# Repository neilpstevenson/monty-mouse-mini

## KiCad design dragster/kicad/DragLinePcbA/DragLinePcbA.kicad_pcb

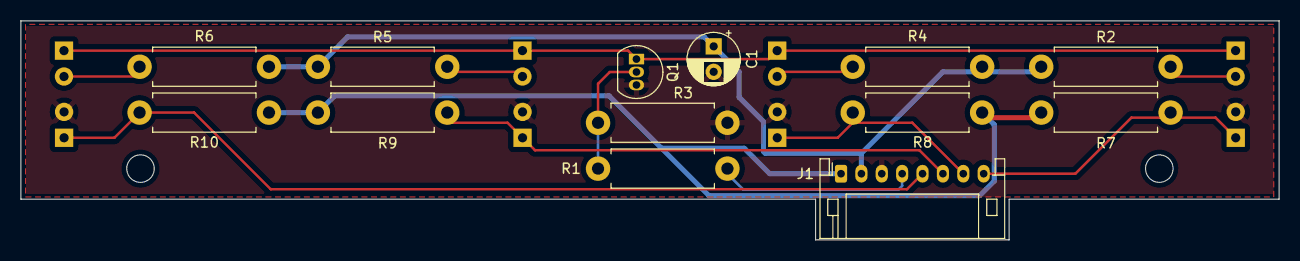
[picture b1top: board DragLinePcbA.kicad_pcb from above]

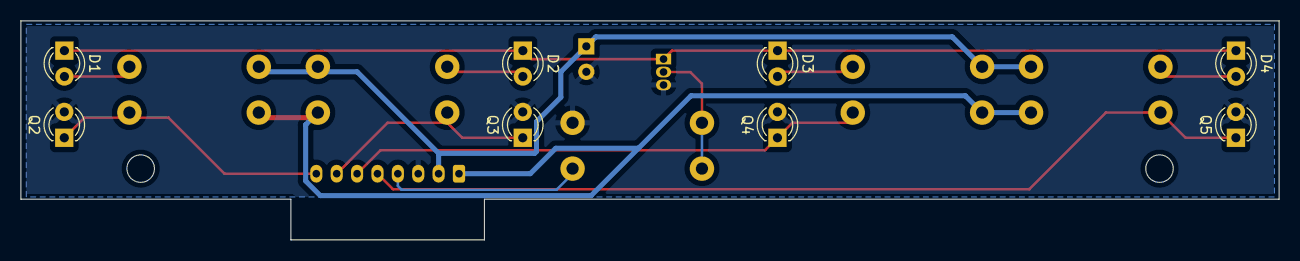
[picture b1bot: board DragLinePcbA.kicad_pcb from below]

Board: 2 copper layers, 123.5 x 21.5 mm, 21 parts (8 on the bottom side), 14 nets.

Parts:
C1: 100uF; CP_Radial_D5.0mm_P2.50mm
D1, D2, D3, D4: LED; LED_D3.0mm_Clear
J1: Conn_01x08_Male; JST_PH_S8B-PH-K_1x08_P2.00mm_Horizontal
Q1: BC337; TO-92_Inline
Q2, Q3, Q4, Q5: SFH309; LED_D3.0mm_Clear
R1: 270R; R_Axial_DIN0411_L9.9mm_D3.6mm_P12.70mm_Horizontal
R2, R4, R5, R6: 27R; R_Axial_DIN0411_L9.9mm_D3.6mm_P12.70mm_Horizontal
R3: 10k; R_Axial_DIN0411_L9.9mm_D3.6mm_P12.70mm_Horizontal
R7, R8, R9, R10: 1.5k; R_Axial_DIN0411_L9.9mm_D3.6mm_P12.70mm_Horizontal

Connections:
+3V3: J1.1, R7.1, R8.1, R9.1, R10.1
+BATT: C1.1, J1.2, R2.1, R4.1, R5.1, R6.1
A0: J1.5, Q5.1 (C), R10.2
A1: J1.6, Q4.1 (C), R9.2
A2: J1.7, Q3.1 (C), R8.2
A3: J1.8, Q2.1 (C), R7.2
D12: J1.4, R1.1
GND: C1.2, J1.3, Q1.3 (E), Q2.2 (E), Q3.2 (E), Q4.2 (E), Q5.2 (E), R3.2
unnamed: D1.1 (K), D2.1 (K), D3.1 (K), D4.1 (K), Q1.1 (C)
unnamed: D1.2 (A), R2.2
unnamed: D2.2 (A), R4.2
unnamed: D3.2 (A), R5.2
unnamed: D4.2 (A), R6.2
unnamed: Q1.2 (B), R1.2, R3.1

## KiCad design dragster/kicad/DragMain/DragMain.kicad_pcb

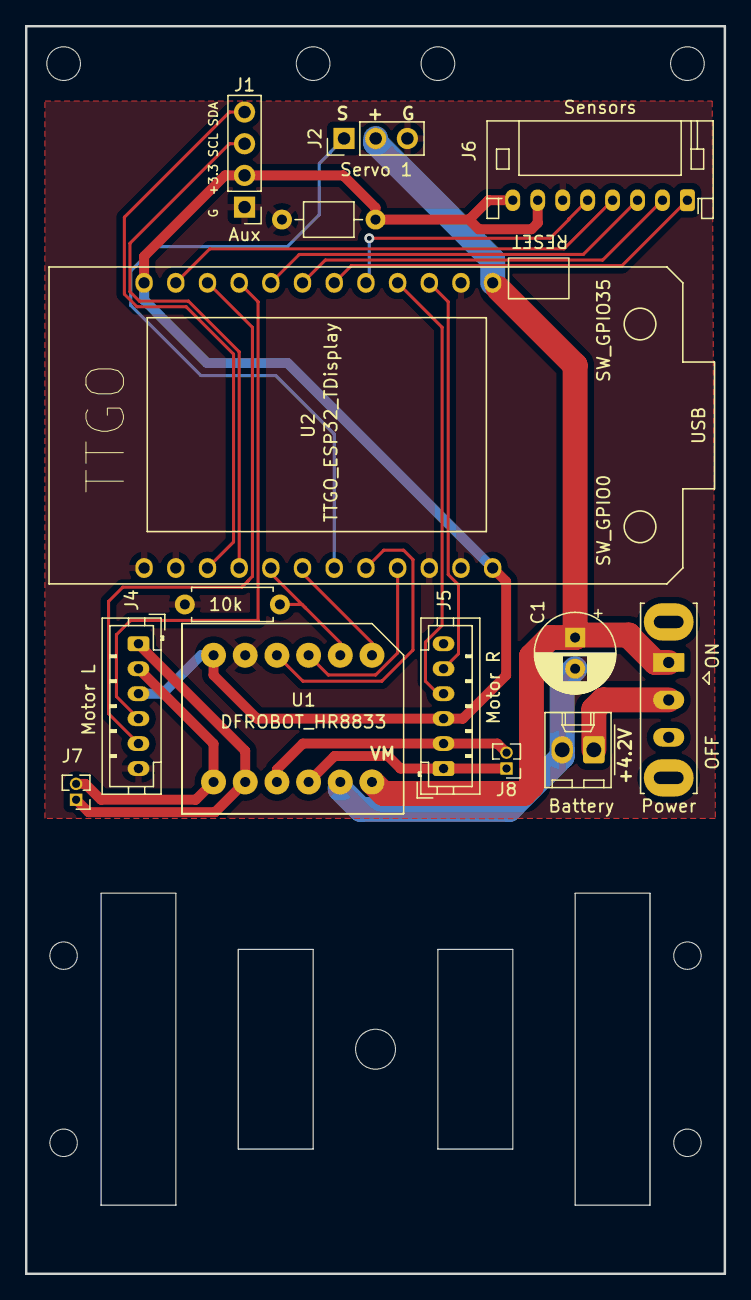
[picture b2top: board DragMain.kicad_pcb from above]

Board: 2 copper layers, 56.0 x 100.0 mm, 14 parts (0 on the bottom side), 24 nets.

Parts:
C1: 330uF; CP_Radial_D6.3mm_P2.50mm
C2: 0.1uF; C_Axial_L3.8mm_D2.6mm_P7.50mm_Horizontal
J1: Aux; PinHeader_1x04_P2.54mm_Vertical
J2: Servo 1; PinHeader_1x03_P2.54mm_Vertical
J3: Battery; Molex_KK-254_AE-6410-02A_1x02_P2.54mm_Vertical
J4: Motor L; JST_PH_B6B-PH-K_1x06_P2.00mm_Vertical
J5: Motor R; JST_PH_B6B-PH-K_1x06_P2.00mm_Vertical
J6: Sensors; JST_PH_S8B-PH-K_1x08_P2.00mm_Horizontal
J7: Motor L2; PinHeader_1x02_P1.27mm_Vertical
J8: Motor R2; PinHeader_1x02_P1.27mm_Vertical
Power: SW_SPST; SW_Slide_1P2T_CK_OS102011MS2Q
R1: 10k; R_Axial_DIN0207_L6.3mm_D2.5mm_P7.62mm_Horizontal
U1: DFROBOT_HR8833
U2: TTGO_ESP32_TDisplay; TTGO_ESP32_TDisplay_New

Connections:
+3V3: C2.2, J1.2, J4.3, J5.3, J6.7, J6.8, U1.6 (VCC), U2.12 (3V3), U2.24 (3V3)
+BATT: C1.1, J2.2, Power.1 (A), U1.12 (VM), U2.13 (5V)
GND: C1.2, C2.1, J1.1, J2.3, J3.2, J4.6, J5.6, J6.6, R1.2, U1.5 (GND), U1.11 (GND), U2.1 (GND), U2.2 (GND), U2.10 (GND), U2.11 (GND), U2.14 (GND)
GPIO2: U1.1 (IA1), U2.6 (IO2)
GPIO12: U1.3 (IB1), U2.9 (IO12)
GPIO13: U1.4 (IB2), U2.8 (IO13)
GPIO15: J2.1, U2.7 (IO15)
GPIO17: R1.1, U1.2 (IA2), U2.5 (IO17)
GPIO21: J1.4, U2.3 (IO21)
GPIO22: J1.3, U2.4 (IO22)
GPIO25: J6.5, U2.17 (IO25)
GPIO26: J5.4, U2.16 (IO26)
GPIO27: J5.5, U2.15 (IO27)
GPIO32: J6.2, U2.19 (IO32)
GPIO33: J6.1, U2.18 (IO33)
GPIO36: J6.4, U2.23 (IO36)
GPIO37: J4.5, U2.22 (IO37)
GPIO38: J4.4, U2.21 (IO38)
GPIO39: J6.3, U2.20 (IO39)
unnamed: J3.1, Power.2 (B)
unnamed: J4.2, J7.2, U1.7 (MA2)
unnamed: J4.1, J7.1, U1.8 (MA1)
unnamed: J5.2, J8.2, U1.9 (MB2)
unnamed: J5.1, J8.1, U1.10 (MB1)

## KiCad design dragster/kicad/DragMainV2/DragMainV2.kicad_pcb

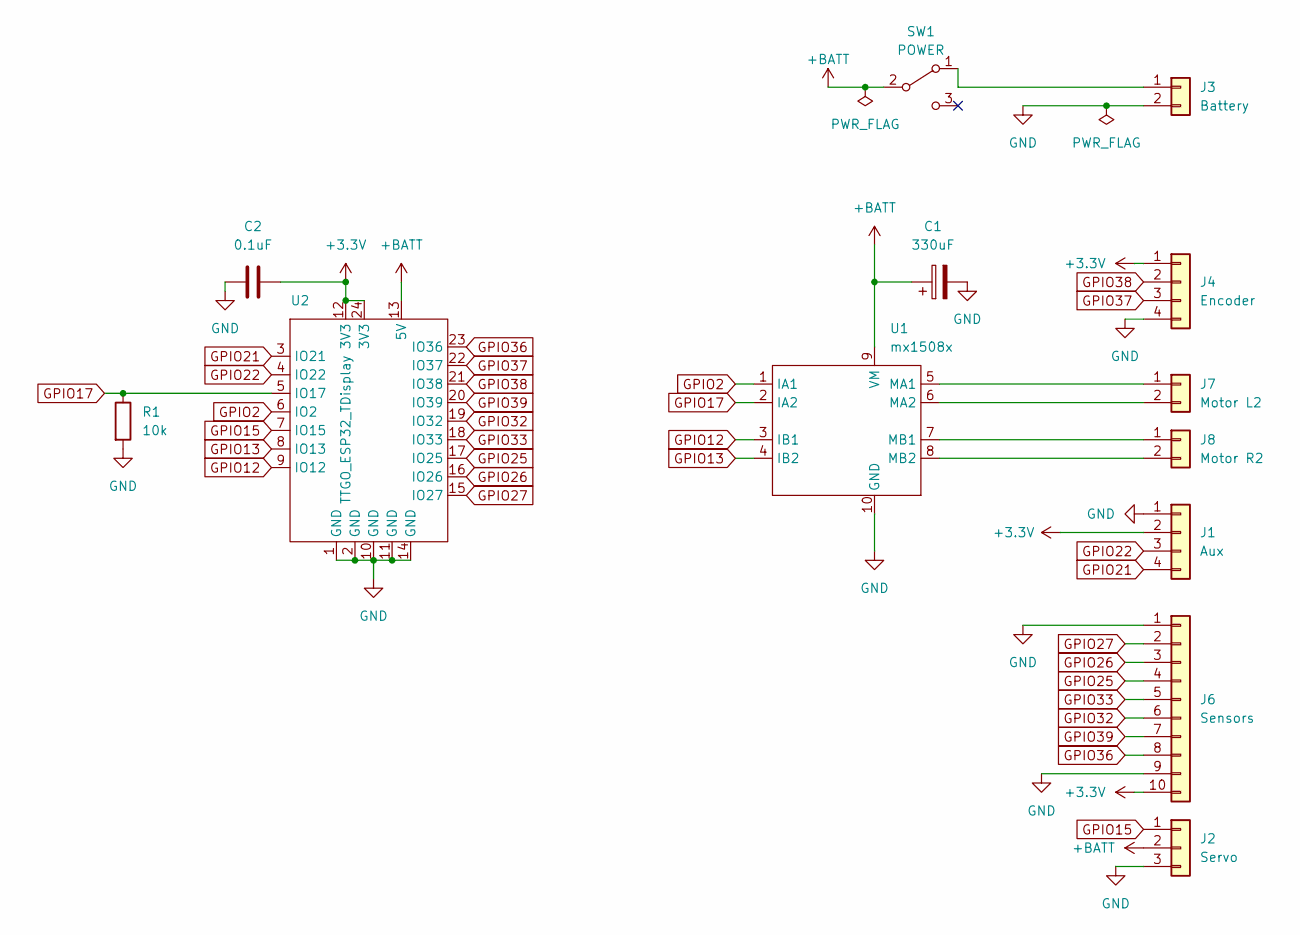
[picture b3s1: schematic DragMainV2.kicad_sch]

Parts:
C1: 330uF; CP_Radial_D6.3mm_P2.50mm
C2: 0.1uF; C_Axial_L3.8mm_D2.6mm_P7.50mm_Horizontal
J1: Aux; PinHeader_1x04_P2.54mm_Vertical
J2: Servo; PinHeader_1x03_P2.54mm_Vertical
J3: Battery; Molex_KK-254_AE-6410-02A_1x02_P2.54mm_Vertical
J4: Encoder; JST_PH_S4B-PH-K_1x04_P2.00mm_Horizontal
J6: Sensors; JST_PH_S10B-PH-K_1x10_P2.00mm_Horizontal
J7: Motor L2; PinHeader_1x02_P1.27mm_Vertical
J8: Motor R2; PinHeader_1x02_P1.27mm_Vertical
R1: 10k; R_Axial_DIN0207_L6.3mm_D2.5mm_P7.62mm_Horizontal
SW1: POWER; SW_Slide_1P1T_Power-Neil
U1: mx1508x
U2: TTGO_ESP32_TDisplay; TTGO_ESP32_TDisplay_New

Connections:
+3.3V: C2.2, J1.2, J4.1, J6.10, U2.12 (3V3), U2.24 (3V3)
+BATT: C1.1, J2.2, SW1.2 (B), U1.9 (VM), U2.13 (5V)
GND: C1.2, C2.1, J1.1, J2.3, J3.2, J4.4, J6.1, J6.9, R1.2, U1.10 (GND), U2.1 (GND), U2.2 (GND), U2.10 (GND), U2.11 (GND), U2.14 (GND)
GPIO2: U1.1 (IA1), U2.6 (IO2)
GPIO12: U1.3 (IB1), U2.9 (IO12)
GPIO13: U1.4 (IB2), U2.8 (IO13)
GPIO15: J2.1, U2.7 (IO15)
GPIO17: R1.1, U1.2 (IA2), U2.5 (IO17)
GPIO21: J1.4, U2.3 (IO21)
GPIO22: J1.3, U2.4 (IO22)
GPIO25: J6.4, U2.17 (IO25)
GPIO26: J6.3, U2.16 (IO26)
GPIO27: J6.2, U2.15 (IO27)
GPIO32: J6.6, U2.19 (IO32)
GPIO33: J6.5, U2.18 (IO33)
GPIO36: J6.8, U2.23 (IO36)
GPIO37: J4.3, U2.22 (IO37)
GPIO38: J4.2, U2.21 (IO38)
GPIO39: J6.7, U2.20 (IO39)
unnamed: J7.1, U1.5 (MA1)
unnamed: J7.2, U1.6 (MA2)
unnamed: J8.1, U1.7 (MB1)
unnamed: J8.2, U1.8 (MB2)
unnamed: J3.1, SW1.1 (A)

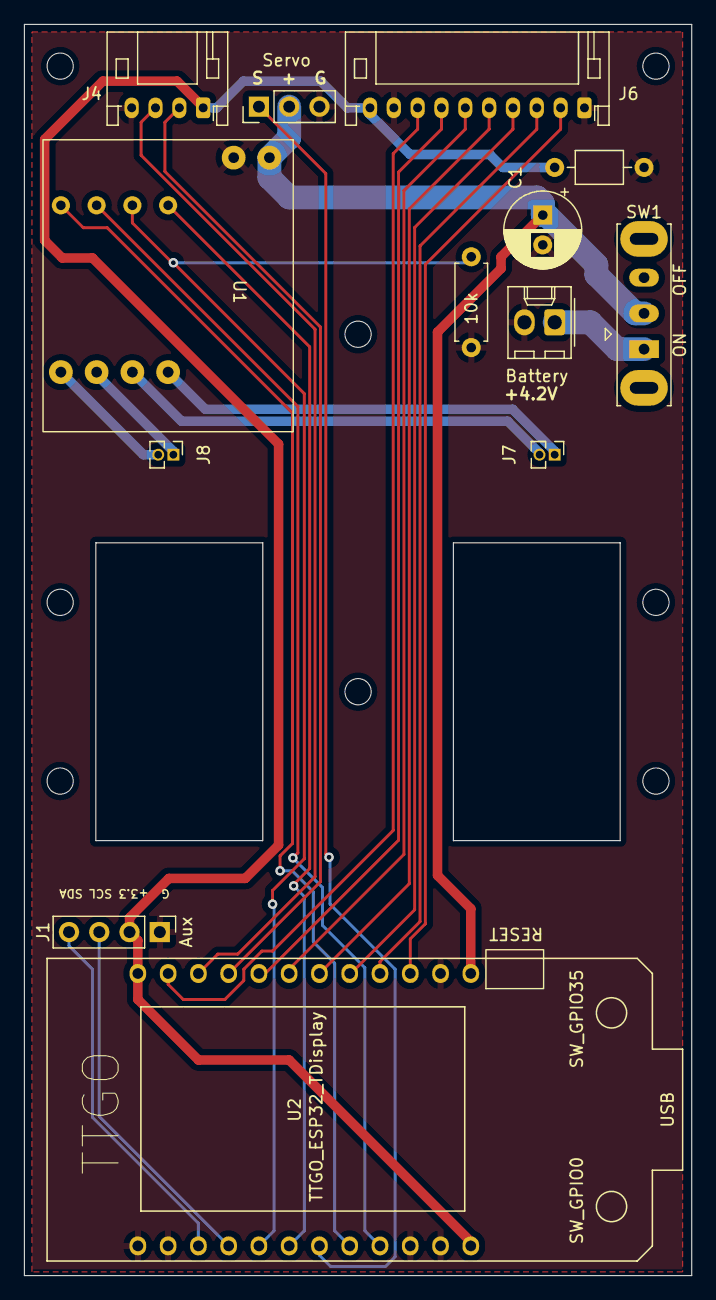
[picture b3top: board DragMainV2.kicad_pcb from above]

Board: 2 copper layers, 56.0 x 105.0 mm, 21 parts (0 on the bottom side), 24 nets.

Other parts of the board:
REFholecentre: locked; MountingHole_2.2mm_M2
REFholeftmr: locked; MountingHole_2.2mm_M2
REFholeleft: locked; MountingHole_2.2mm_M2
REFholemidfront: locked; MountingHole_2.2mm_M2
REFholeright: locked; MountingHole_2.2mm_M2
REFholerightmf: locked; MountingHole_2.2mm_M2
REFholerightmr: locked; MountingHole_2.2mm_M2
REFleftmf: locked; MountingHole_2.2mm_M2

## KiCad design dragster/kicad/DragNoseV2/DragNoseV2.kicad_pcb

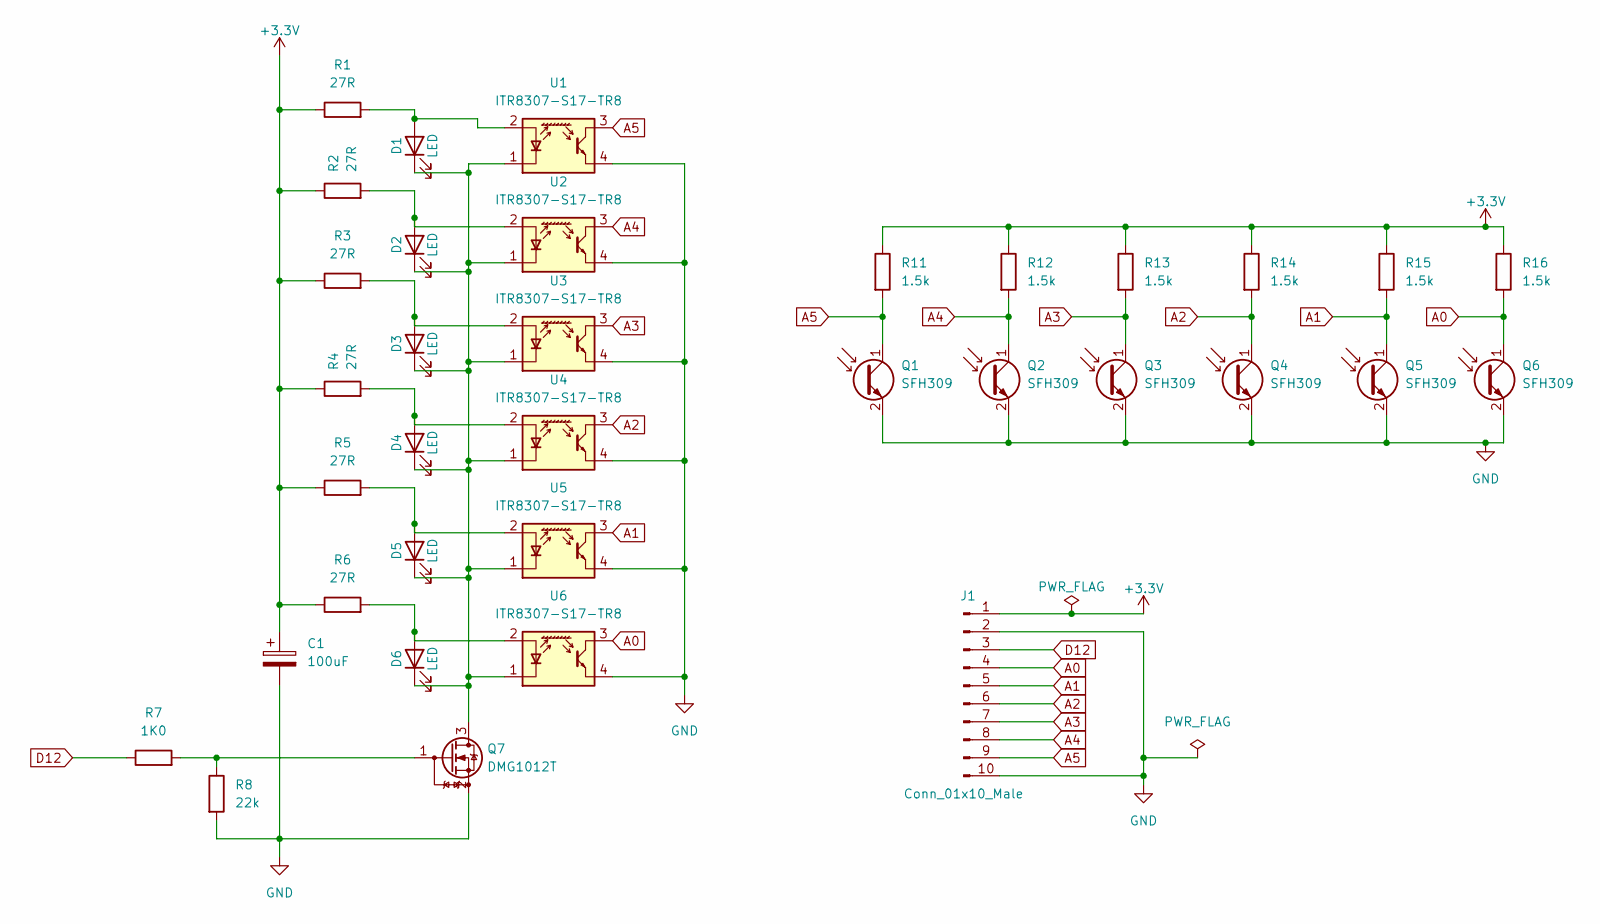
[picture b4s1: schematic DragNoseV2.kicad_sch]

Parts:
C1: 100uF; C_Elec_5x5.8
D1, D2, D3, D4, D5, D6: LED; LED_D3.0mm_Clear
J1: Conn_01x10_Male; JST_PH_S10B-PH-K_1x10_P2.00mm_Horizontal
Q1, Q2, Q3, Q4, Q5, Q6: SFH309; LED_D3.0mm_Clear
Q7: DMG1012T; SOT-523
R1, R2, R3, R4, R5, R6: 27R; R_0805_2012Metric_Pad1.20x1.40mm_HandSolder
R7: 1K0; R_0805_2012Metric_Pad1.20x1.40mm_HandSolder
R8: 22k; R_0805_2012Metric_Pad1.20x1.40mm_HandSolder
R11, R12, R13, R14, R15, R16: 1.5k; R_0805_2012Metric_Pad1.20x1.40mm_HandSolder
U1, U2, U3, U4, U5, U6: ITR8307-S17-TR8; Everlight_ITR1201SR10AR

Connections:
+3.3V: C1.1, J1.1, R1.1, R2.1, R3.1, R4.1, R5.1, R6.1, R11.1, R12.1, R13.1, R14.1, R15.1, R16.1
A0: J1.4, Q6.1 (C), R16.2, U6.3
A1: J1.5, Q5.1 (C), R15.2, U5.3
A2: J1.6, Q4.1 (C), R14.2, U4.3
A3: J1.7, Q3.1 (C), R13.2, U3.3
A4: J1.8, Q2.1 (C), R12.2, U2.3
A5: J1.9, Q1.1 (C), R11.2, U1.3
D12: J1.3, R7.1
GND: C1.2, J1.2, J1.10, Q1.2 (E), Q2.2 (E), Q3.2 (E), Q4.2 (E), Q5.2 (E), Q6.2 (E), Q7.2 (S), R8.2, U1.4, U2.4, U3.4, U4.4, U5.4, U6.4
unnamed: D1.2 (A), R1.2, U1.2 (A)
unnamed: D2.2 (A), R2.2, U2.2 (A)
unnamed: D3.2 (A), R3.2, U3.2 (A)
unnamed: D4.2 (A), R4.2, U4.2 (A)
unnamed: D5.2 (A), R5.2, U5.2 (A)
unnamed: D1.1 (K), D2.1 (K), D3.1 (K), D4.1 (K), D5.1 (K), D6.1 (K), Q7.3 (D), U1.1 (K), U2.1 (K), U3.1 (K), U4.1 (K), U5.1 (K), U6.1 (K)
unnamed: D6.2 (A), R6.2, U6.2 (A)
unnamed: Q7.1 (G), R7.2, R8.1

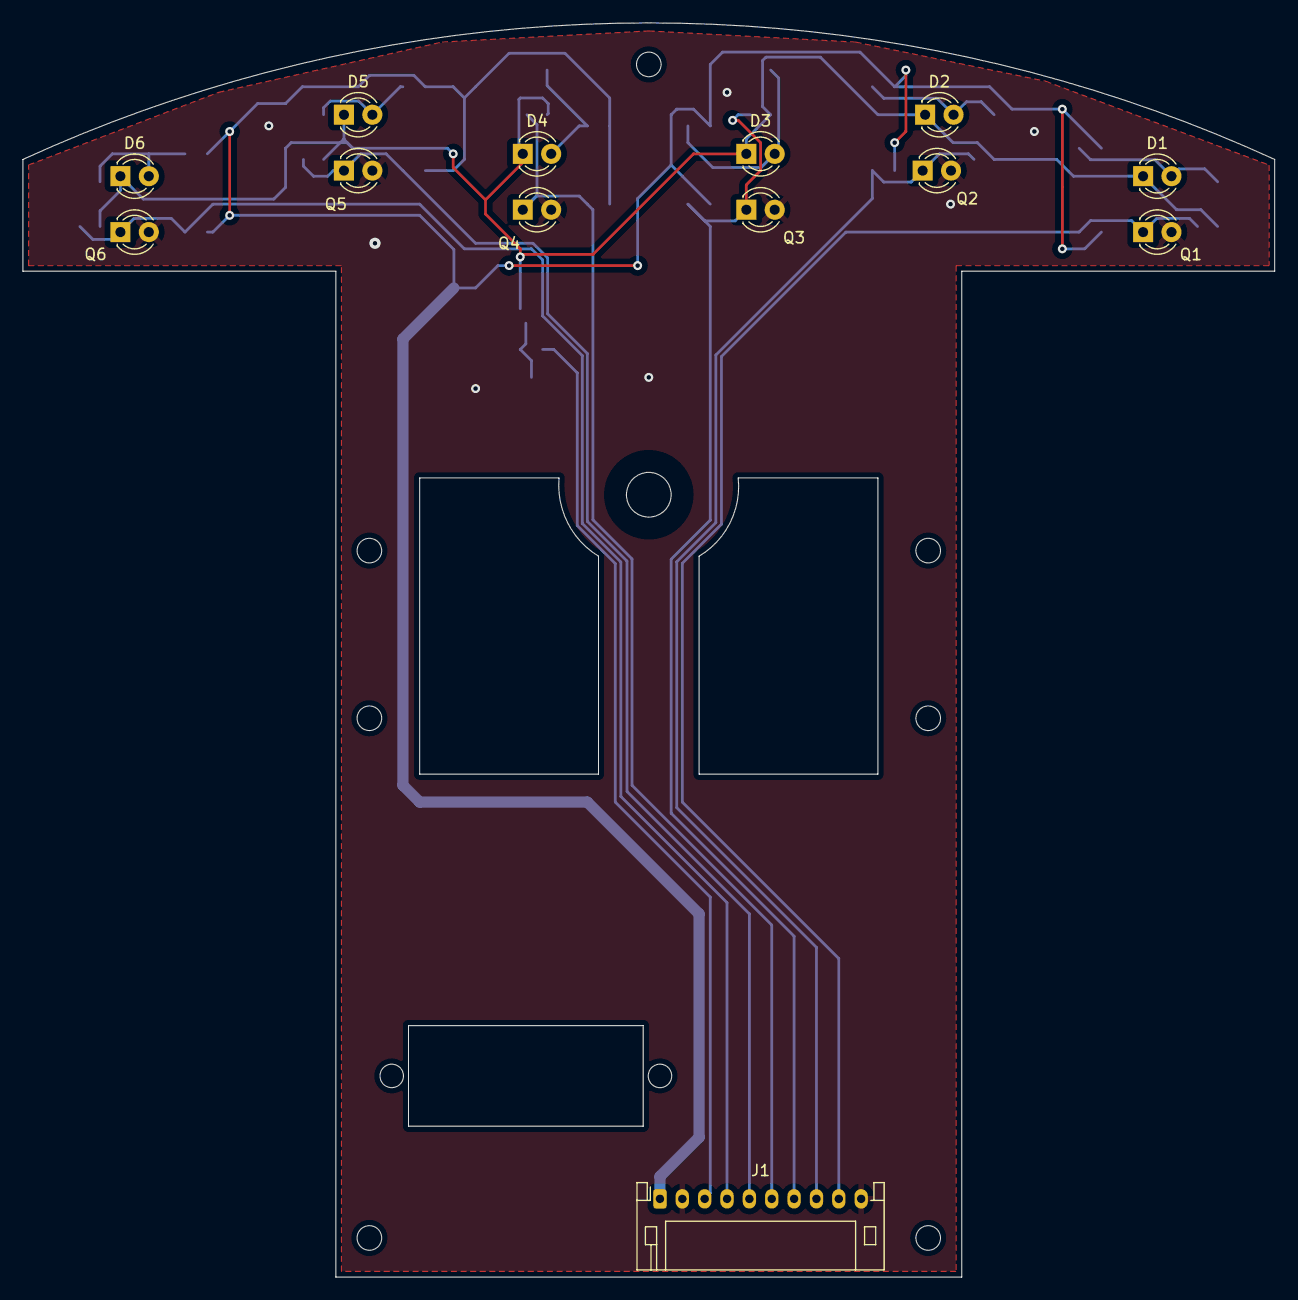
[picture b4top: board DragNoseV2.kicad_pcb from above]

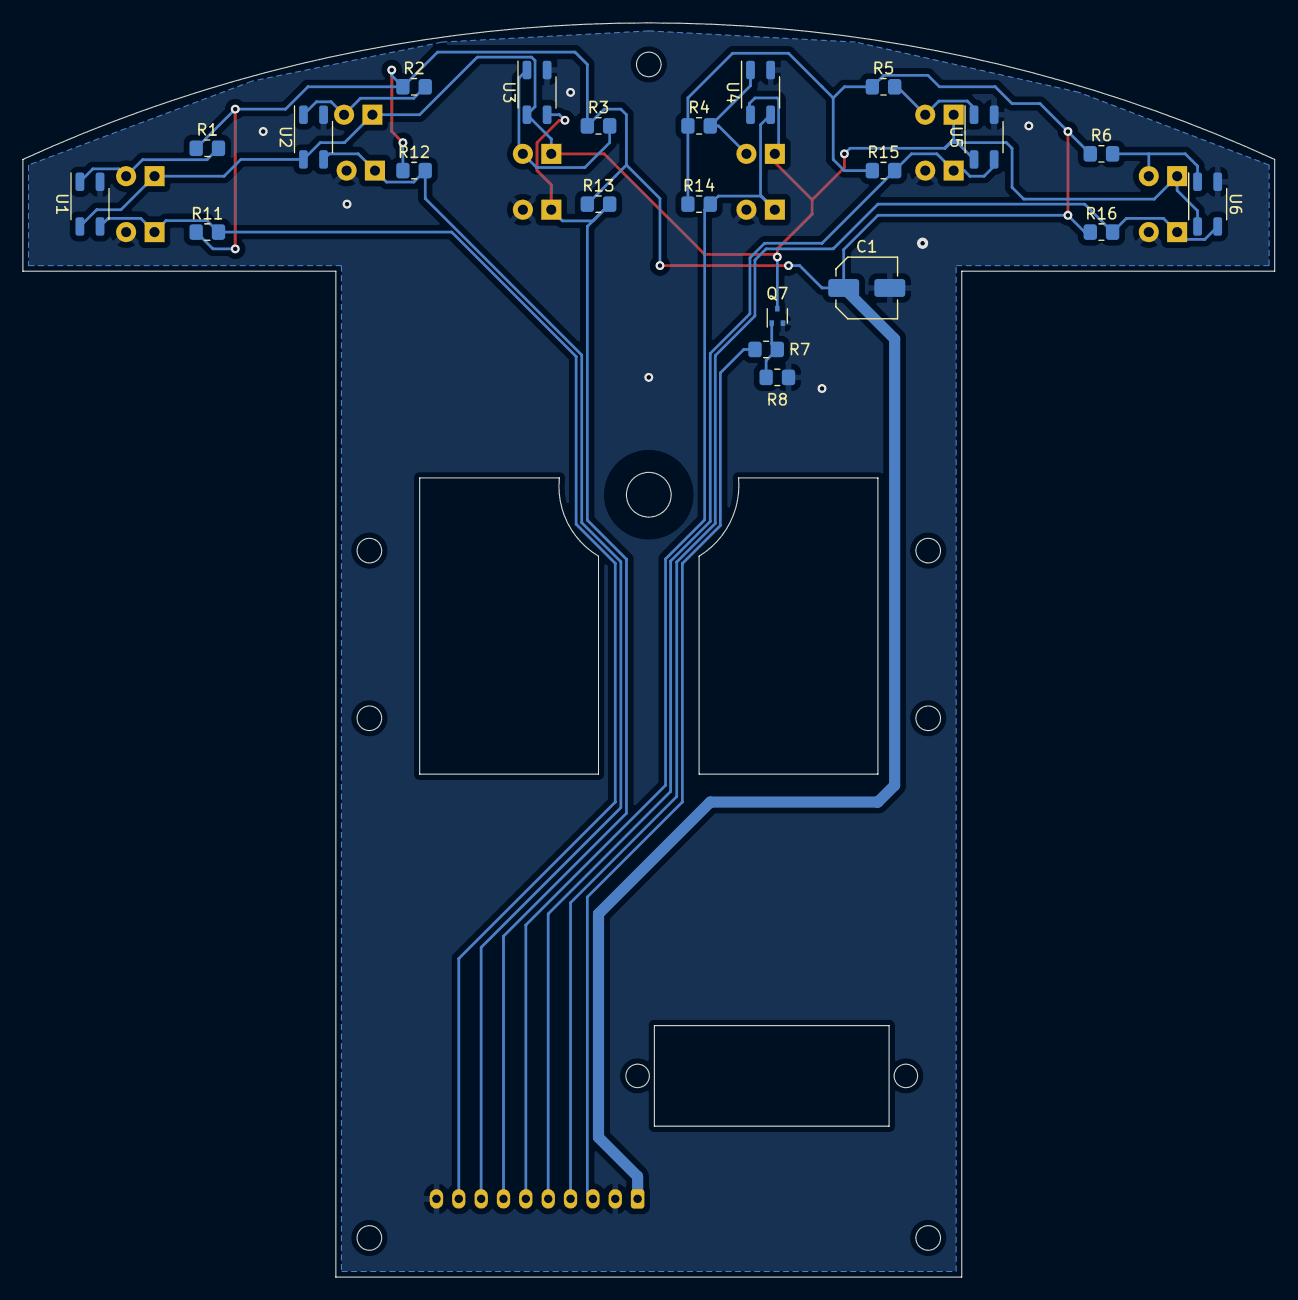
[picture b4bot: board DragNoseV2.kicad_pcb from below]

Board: 2 copper layers, 112.0 x 112.2 mm, 41 parts (22 on the bottom side), 17 nets.

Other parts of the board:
REFaxle: MountingHole_4mm
REFholeftmr: locked; MountingHole_2.2mm_M2
REFholerightmf: locked; MountingHole_2.2mm_M2
REFholerightmf#2: locked; MountingHole_2.2mm_M2
REFholerightmr: locked; MountingHole_2.2mm_M2
REFleftmf: locked; MountingHole_2.2mm_M2

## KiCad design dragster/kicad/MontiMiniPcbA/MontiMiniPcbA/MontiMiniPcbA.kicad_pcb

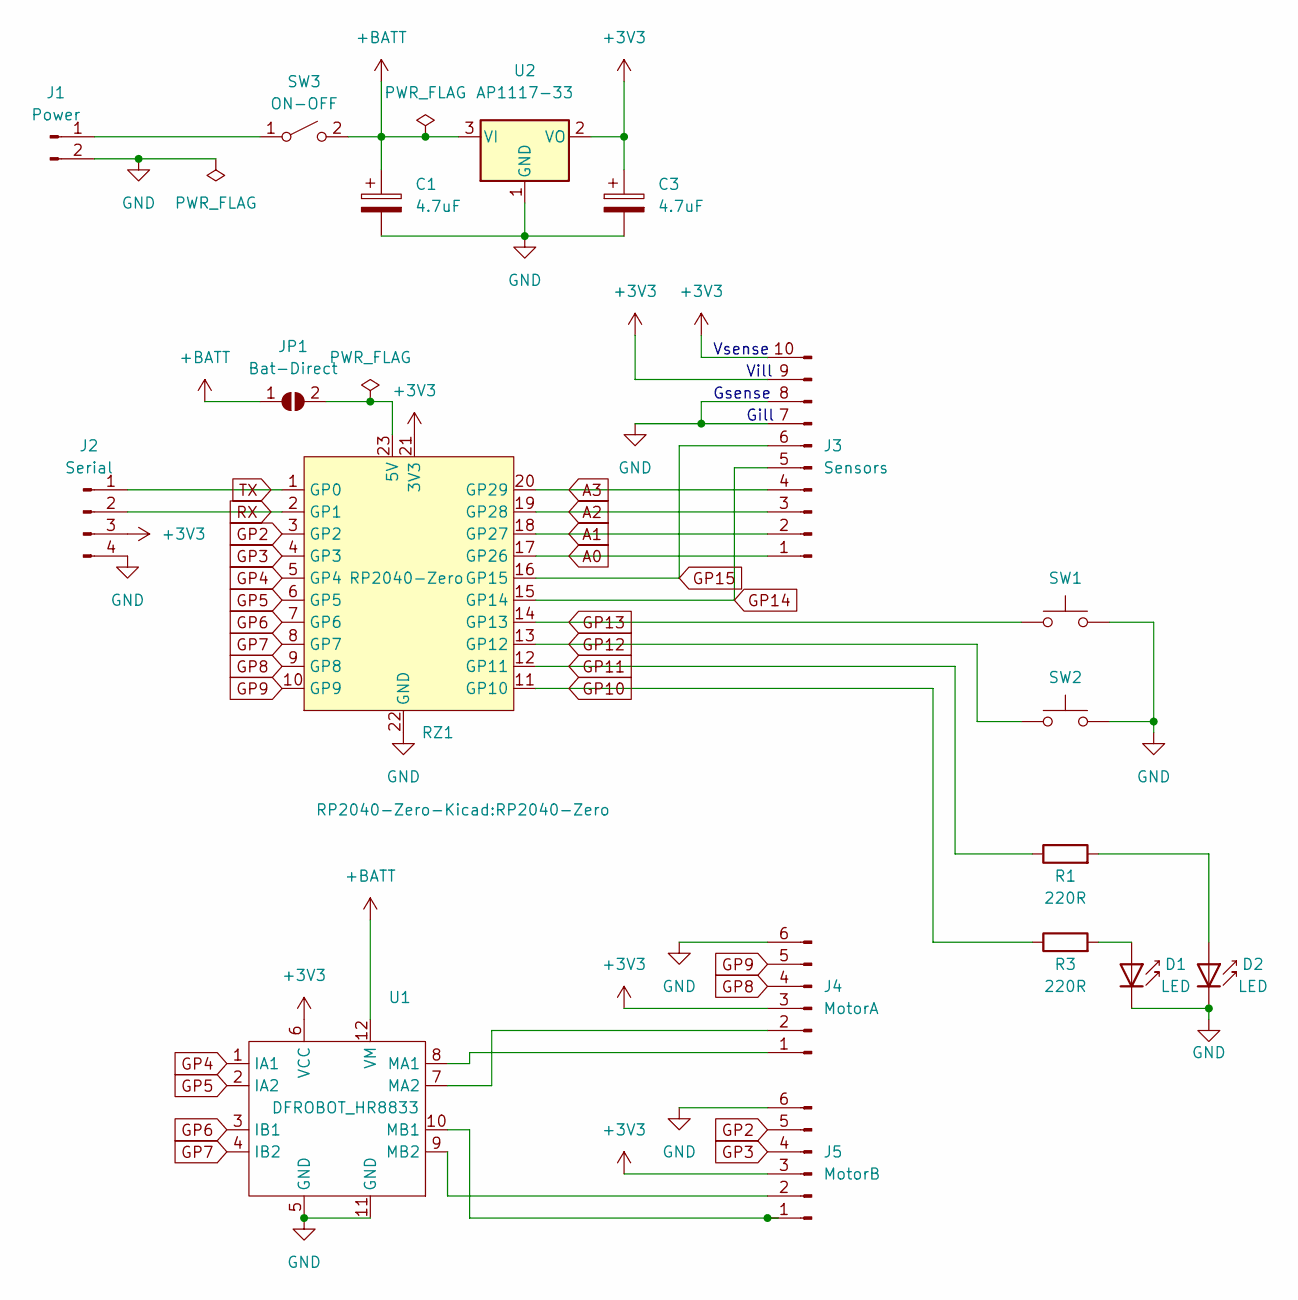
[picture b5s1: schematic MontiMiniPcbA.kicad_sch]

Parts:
C1, C3: 4.7uF; C_0805_2012Metric_Pad1.18x1.45mm_HandSolder
D1, D2: LED; LED_D3.0mm
J1: Power
J2: Serial; PinHeader_1x04_P2.54mm_Vertical
J3: Sensors; PinHeader_1x10_P1.27mm_Vertical
J4: MotorA; PinHeader_1x06_P1.27mm_Vertical
J5: MotorB; PinHeader_1x06_P1.27mm_Vertical
JP1: Bat-Direct; SolderJumper-2_P1.3mm_Open_Pad1.0x1.5mm
R1, R3: 220R; R_0805_2012Metric_Pad1.20x1.40mm_HandSolder
RZ1: RP2040-Zero
SW1, SW2: SW_Push; SW_Push_SPST_NO_Alps_SKRK
SW3: ON-OFF; SW_SPDT_PCM12
U1: DFROBOT_HR8833
U2: AP1117-33; SOT-223-3_TabPin2

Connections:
+3V3: C3.1, J2.3, J3.9, J3.10, J4.3, J5.3, RZ1.21 (3V3), U1.6 (VCC), U2.2 (VO)
+BATT: C1.1, JP1.1 (A), SW3.2 (B), U1.12 (VM), U2.3 (VI)
A0: J3.1, RZ1.17 (GP26)
A1: J3.2, RZ1.18 (GP27)
A2: J3.3, RZ1.19 (GP28)
A3: J3.4, RZ1.20 (GP29)
GND: C1.2, C3.2, D1.1 (K), D2.1 (K), J1.2, J2.4, J3.7, J3.8, J4.6, J5.6, RZ1.22 (GND), SW1.2, SW2.2, U1.5 (GND), U1.11 (GND), U2.1 (GND)
GP2: J5.5, RZ1.3 (GP2)
GP3: J5.4, RZ1.4 (GP3)
GP4: RZ1.5 (GP4), U1.1 (IA1)
GP5: RZ1.6 (GP5), U1.2 (IA2)
GP6: RZ1.7 (GP6), U1.3 (IB1)
GP7: RZ1.8 (GP7), U1.4 (IB2)
GP8: J4.4, RZ1.9 (GP8)
GP9: J4.5, RZ1.10 (GP9)
GP10: R3.1, RZ1.11 (GP10)
GP11: R1.1, RZ1.12 (GP11)
GP12: RZ1.13 (GP12), SW2.1
GP13: RZ1.14 (GP13), SW1.1
GP14: J3.5, RZ1.15 (GP14)
GP15: J3.6, RZ1.16 (GP15)
unnamed: D1.2 (A), R3.2
unnamed: D2.2 (A), R1.2
unnamed: J1.1, SW3.1 (A)
unnamed: J4.1, U1.8 (MA1)
unnamed: J4.2, U1.7 (MA2)
unnamed: J5.1, U1.10 (MB1)
unnamed: J5.2, U1.9 (MB2)
unnamed: JP1.2 (B), RZ1.23 (5V)
RX: J2.2, RZ1.2 (GP1)
TX: J2.1, RZ1.1 (GP0)

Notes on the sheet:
Gsense
Gill
Vsense
Vill

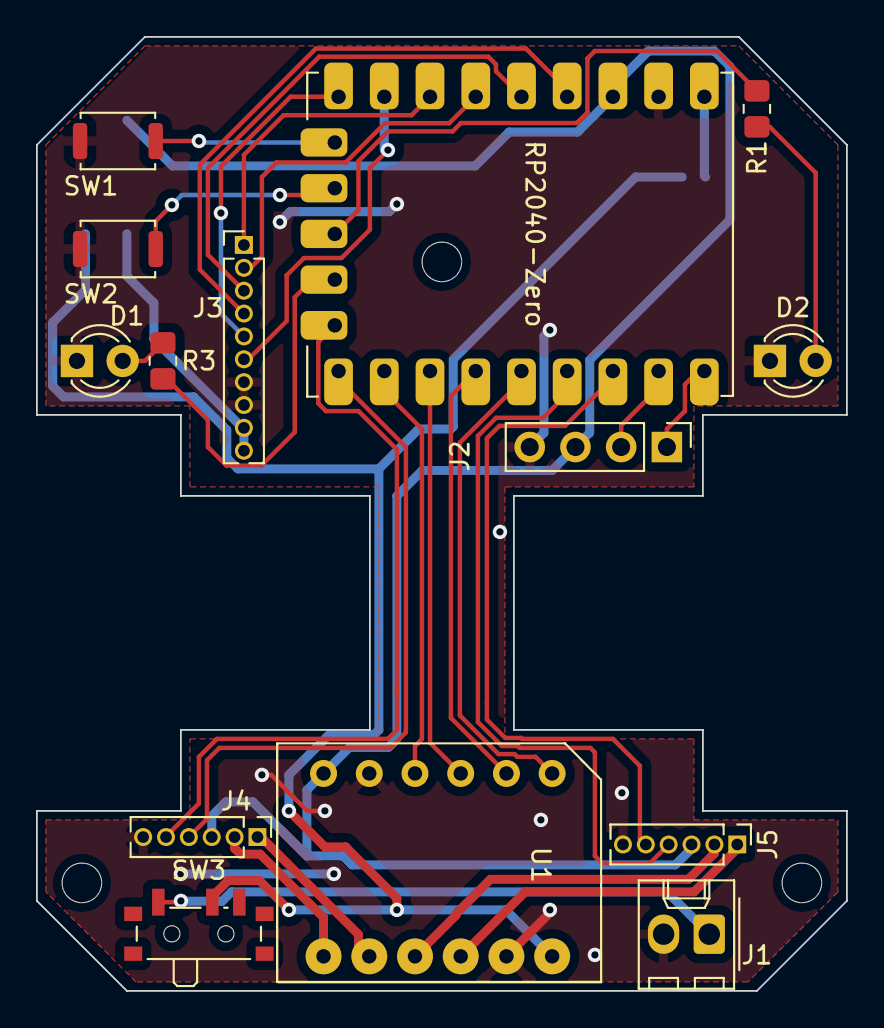
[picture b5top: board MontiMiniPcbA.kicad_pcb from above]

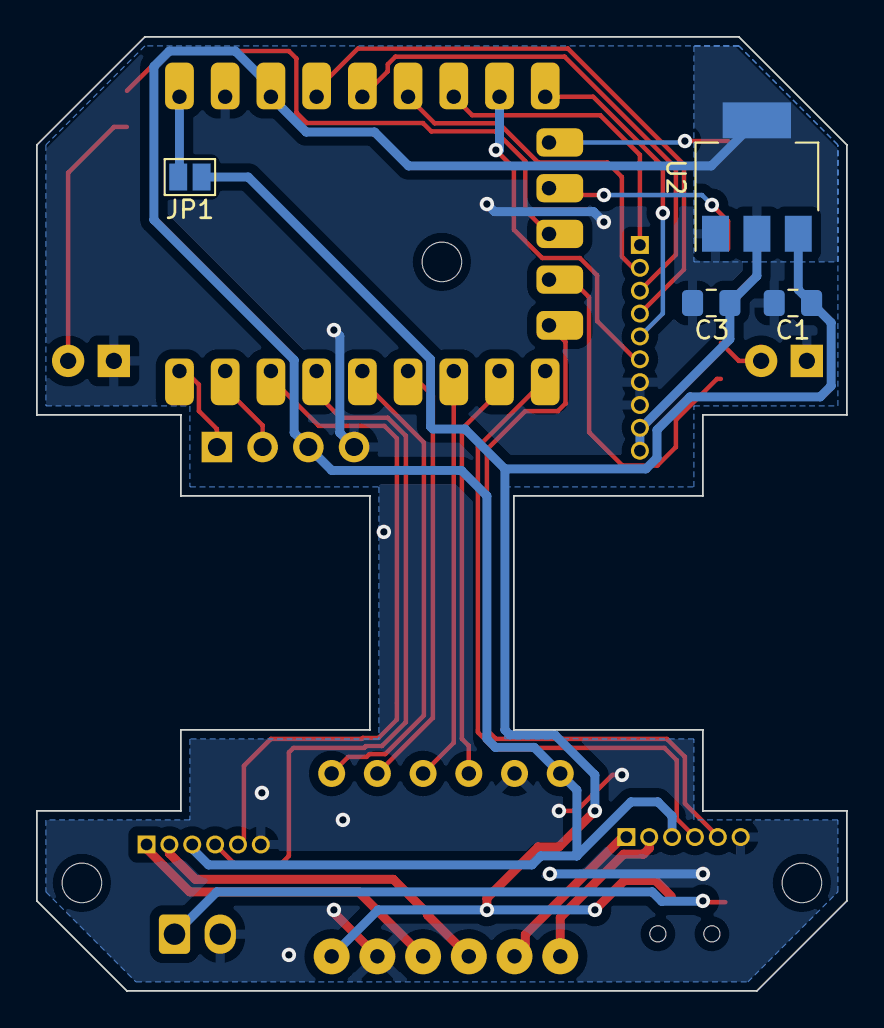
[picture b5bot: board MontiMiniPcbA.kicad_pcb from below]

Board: 2 copper layers, 45.0 x 53.0 mm, 21 parts (5 on the bottom side), 31 nets.

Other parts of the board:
REFH1, REFH2, REFH3: MountingHole_2.2mm_M2

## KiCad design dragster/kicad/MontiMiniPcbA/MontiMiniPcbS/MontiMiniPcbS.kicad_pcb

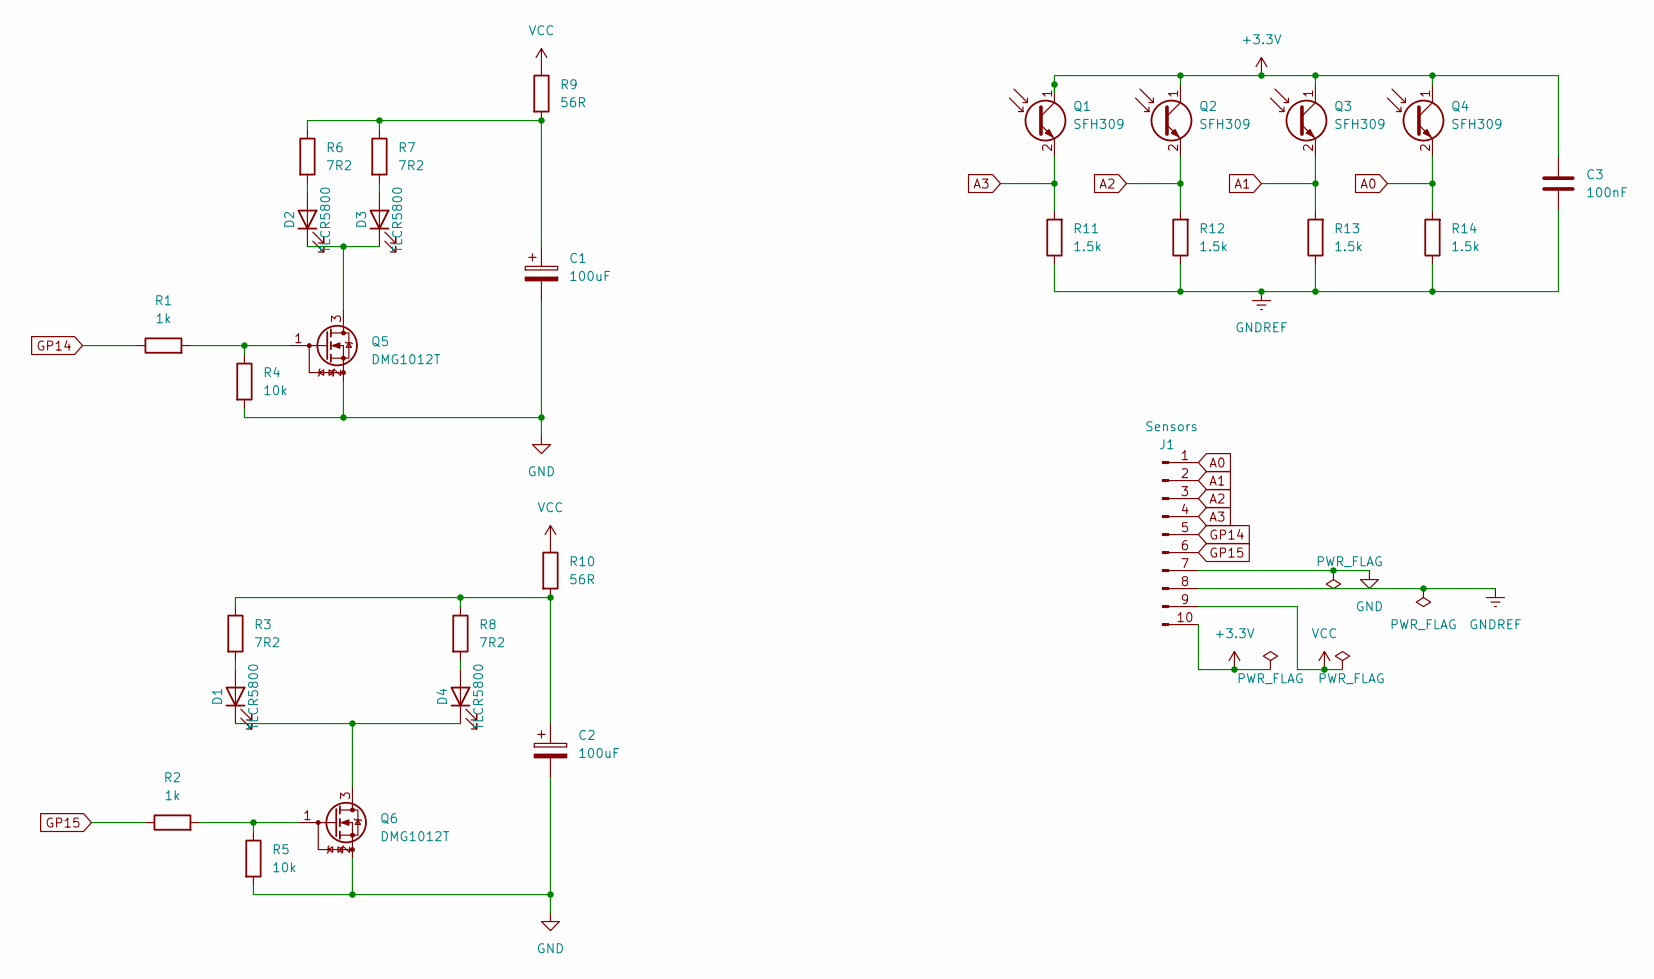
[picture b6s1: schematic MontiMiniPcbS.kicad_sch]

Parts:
C1, C2: 100uF; CP_Elec_6.3x5.9
C3: 100nF; C_0805_2012Metric_Pad1.18x1.45mm_HandSolder
D1, D2, D3, D4: TLCR5800
J1: Sensors; PinHeader_1x10_P1.27mm_Vertical
Q1, Q2, Q3, Q4: SFH309; LED_D3.0mm_Horizontal_O1.27mm_Z2.0mm
Q5, Q6: DMG1012T; SOT-323_SC-70_Handsoldering
R1, R2: 1k; R_0805_2012Metric_Pad1.20x1.40mm_HandSolder
R3, R6, R7, R8: 7R2; R_0805_2012Metric_Pad1.20x1.40mm_HandSolder
R4, R5: 10k; R_0805_2012Metric_Pad1.20x1.40mm_HandSolder
R9, R10: 56R; R_0805_2012Metric_Pad1.20x1.40mm_HandSolder
R11, R12, R13, R14: 1.5k; R_0805_2012Metric_Pad1.20x1.40mm_HandSolder

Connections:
+3V3: C3.1, J1.10, Q1.1 (C), Q2.1 (C), Q3.1 (C), Q4.1 (C)
A0: J1.1, Q4.2 (E), R14.2
A1: J1.2, Q3.2 (E), R13.2
A2: J1.3, Q2.2 (E), R12.2
A3: J1.4, Q1.2 (E), R11.2
GND: C1.2, C2.2, J1.7, Q5.2 (S), Q6.2 (S), R4.2, R5.2
GNDREF: C3.2, J1.8, R11.1, R12.1, R13.1, R14.1
GP14: J1.5, R1.1
GP15: J1.6, R2.1
unnamed: C1.1, R6.1, R7.1, R9.2
unnamed: C2.1, R3.1, R8.1, R10.2
unnamed: D1.1 (K), D4.1 (K), Q6.3 (D)
unnamed: D1.2 (A), R3.2
unnamed: D2.1 (K), D3.1 (K), Q5.3 (D)
unnamed: D2.2 (A), R6.2
unnamed: D3.2 (A), R7.2
unnamed: D4.2 (A), R8.2
unnamed: Q5.1 (G), R1.2, R4.1
unnamed: Q6.1 (G), R2.2, R5.1
VCC: J1.9, R9.1, R10.1

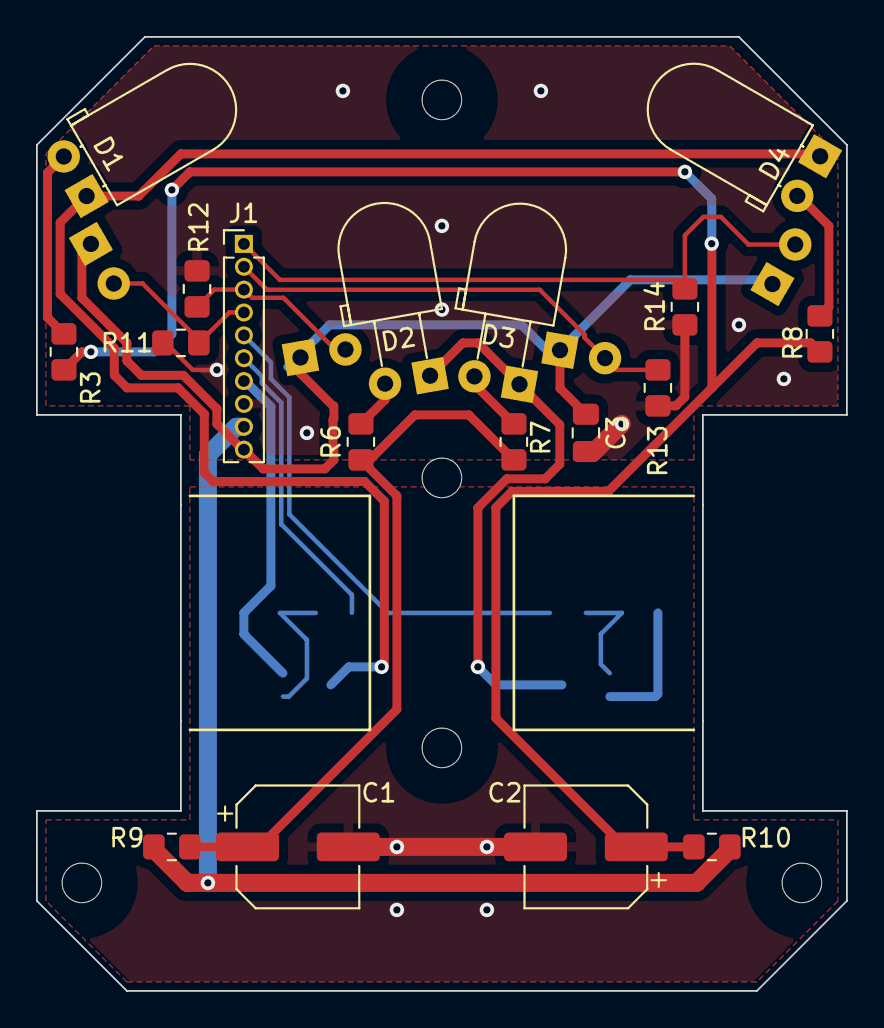
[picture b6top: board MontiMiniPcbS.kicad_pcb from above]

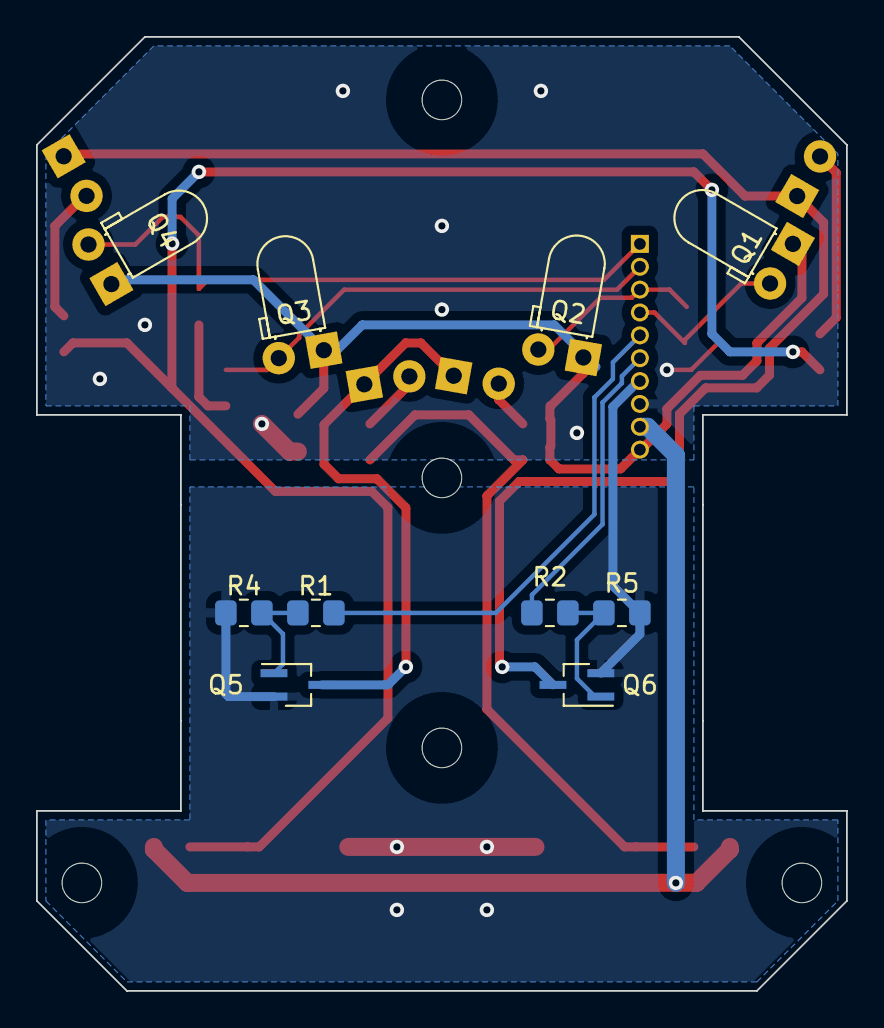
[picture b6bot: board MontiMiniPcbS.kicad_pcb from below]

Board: 2 copper layers, 45.0 x 53.0 mm, 33 parts (10 on the bottom side), 20 nets.

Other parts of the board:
REFH1, REFH1#2, REFH1#3, REFH2, REFH3: MountingHole_2.2mm_M2

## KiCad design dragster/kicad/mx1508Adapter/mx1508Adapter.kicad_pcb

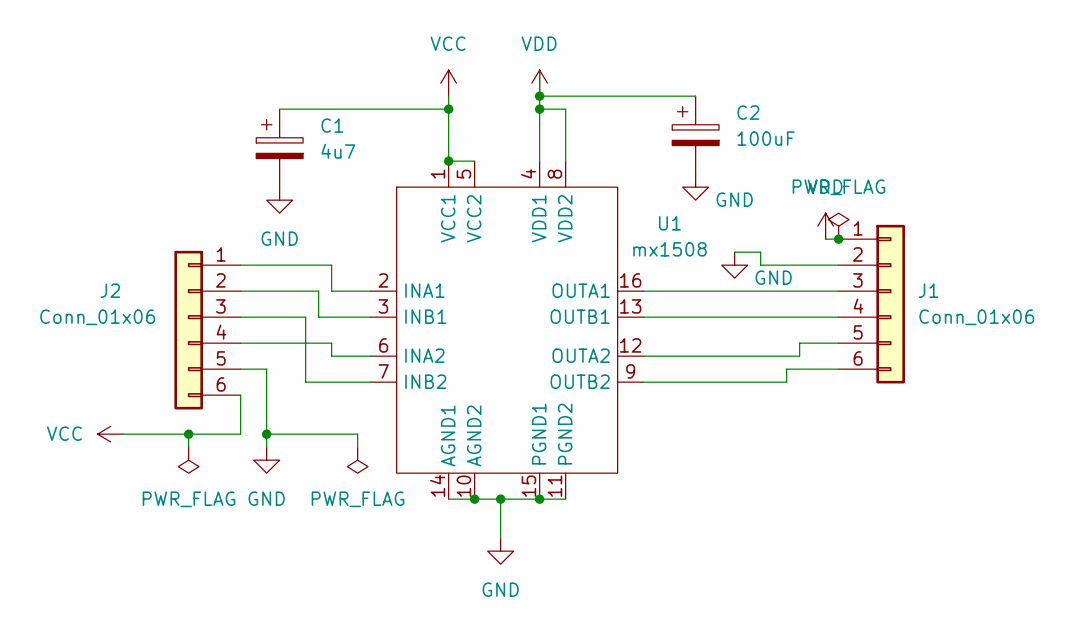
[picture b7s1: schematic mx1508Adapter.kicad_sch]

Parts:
C1: 4u7; C_0805_2012Metric
C2: 100uF; CP_Elec_6.3x5.4
J1, J2: Conn_01x06; PinHeader_1x06_P2.54mm_Vertical
U1: mx1508; SOP-16_4.55x10.3mm_P1.27mm

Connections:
GND: C1.2, C2.2, J1.2, J2.5, U1.10 (AGND2), U1.11 (PGND2), U1.14 (AGND1), U1.15 (PGND1)
unnamed: J1.3, U1.16 (OUTA1)
unnamed: J1.4, U1.13 (OUTB1)
unnamed: J1.5, U1.12 (OUTA2)
unnamed: J1.6, U1.9 (OUTB2)
unnamed: J2.1, U1.2 (INA1)
unnamed: J2.2, U1.3 (INB1)
unnamed: J2.3, U1.7 (INB2)
unnamed: J2.4, U1.6 (INA2)
VCC: C1.1, J2.6, U1.1 (VCC1), U1.5 (VCC2)
VDD: C2.1, J1.1, U1.4 (VDD1), U1.8 (VDD2)

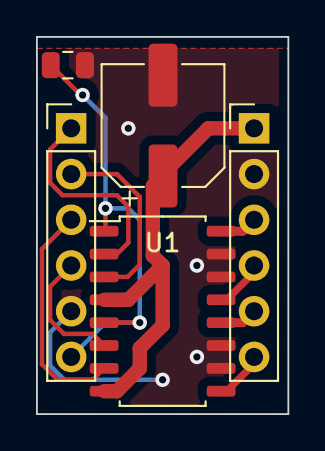
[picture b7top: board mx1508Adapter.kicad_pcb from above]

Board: 2 copper layers, 14.0 x 21.0 mm, 5 parts (0 on the bottom side), 11 nets.
